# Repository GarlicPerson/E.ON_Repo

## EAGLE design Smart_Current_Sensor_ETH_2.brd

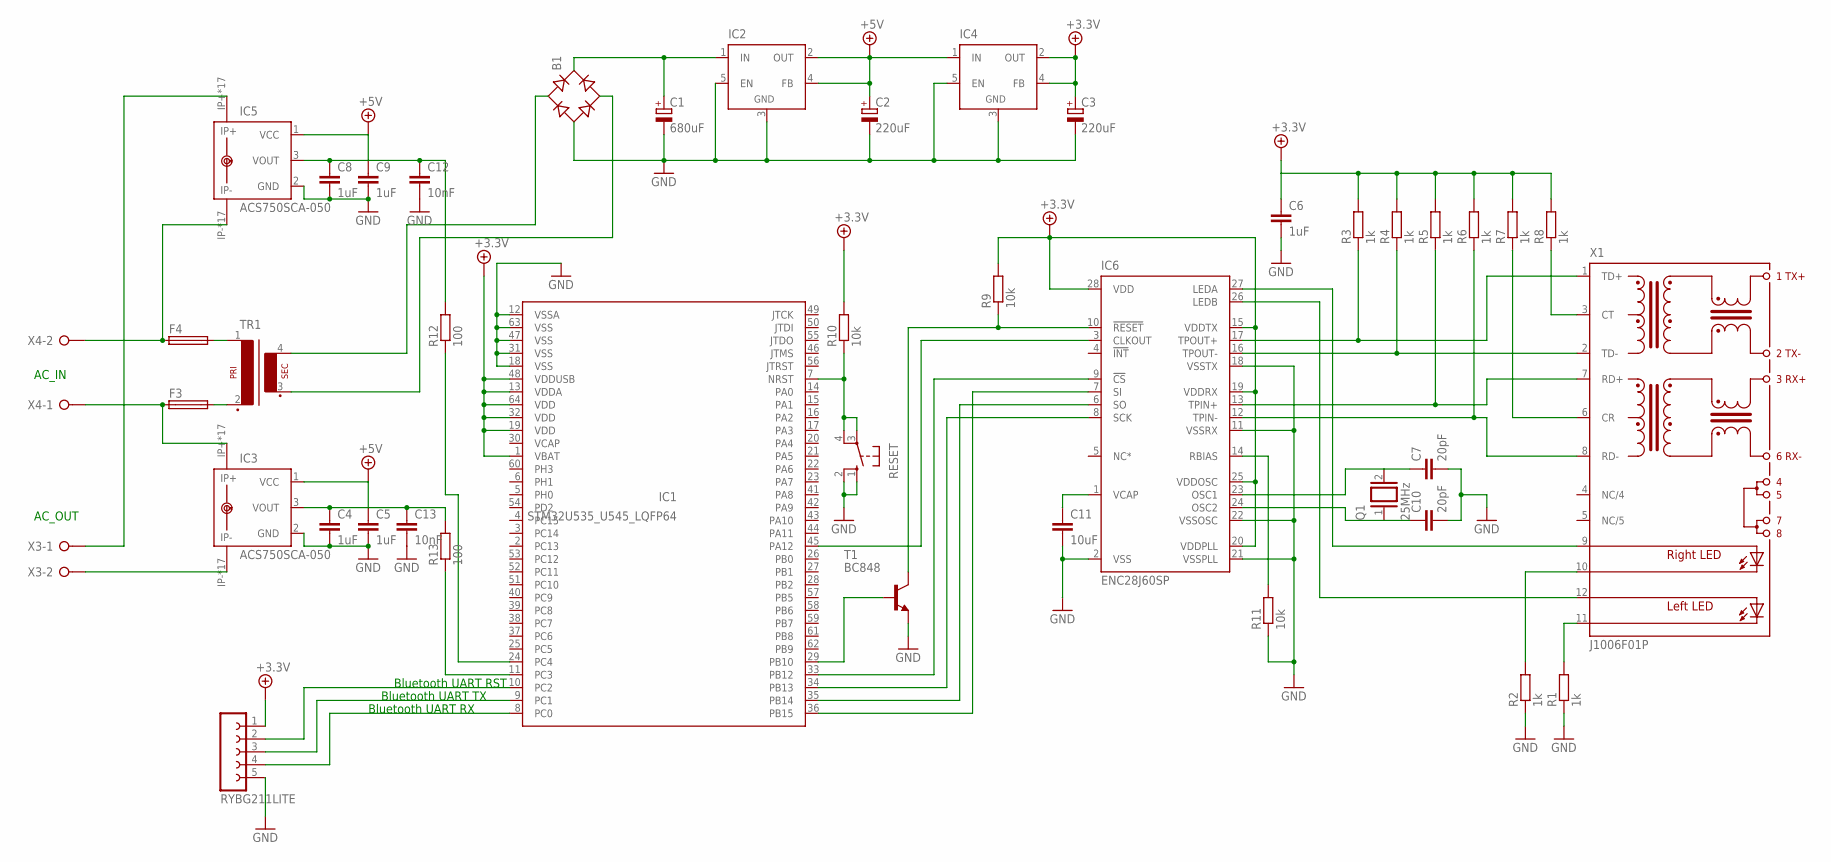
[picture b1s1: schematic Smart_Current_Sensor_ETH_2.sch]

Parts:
B1: B-DIL
C1: 680uF; 153CLV-0405
C2, C3: 220uF; 153CLV-0405
C4, C5, C6, C8, C9: 1uF; C1210
C7, C10: 20pF; C1210
C11: 10uF; C1210
C12, C13: 10nF; C1210
F3, F4: KS9V
IC1: STM32U535_U545_LQFP64; LQFP64_PACKAGE
IC2, IC4: LM2596TH; TO220-52
IC3, IC5: ACS750SCA-050; ACS75050
IC6: ENC28J60SP; DIL28-3
Q1: 25MHz; QS
R1, R2, R3, R4, R5, R6, R7, R8: 1k; R1206
R9, R10, R11: 10k; R1206
R12, R13: 100; R1206
RESET: 10-XX; B3F-10XX
RYBG211LITE: FE05-1
T1: BC848; SOT23
TR1: VR04,5-1
X1: J1006F01P; J1
X3, X4: W237-02P; W237-132

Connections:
+5V: C2.+, C3.+, C5.1, C6.1, C9.1, IC1.1 (VBAT), IC1.13 (VDDA), IC1.19 (VDD), IC1.32 (VDD), IC1.48 (VDDUSB), IC1.64 (VDD), IC2.2 (OUT), IC2.4 (FB), IC3.1 (VCC), IC4.1 (IN), IC4.2 (OUT), IC4.4 (FB), IC5.1 (VCC), IC6.15 (VDDTX), IC6.19 (VDDRX), IC6.20 (VDDPLL), IC6.25 (VDDOSC), IC6.28 (VDD), R3.2, R4.2, R5.2, R6.2, R7.2, R8.2, R9.2, R10.2, RYBG211LITE.1
GND: B1.-, C1.-, C2.-, C3.-, C4.2, C5.2, C6.2, C7.2, C8.2, C9.2, C10.2, C11.2, C12.2, C13.2, IC1.12 (VSSA), IC1.18 (VSS), IC1.31 (VSS), IC1.47 (VSS), IC1.63 (VSS), IC2.3 (GND), IC2.5 (EN), IC3.2 (GND), IC4.3 (GND), IC4.5 (EN), IC5.2 (GND), IC6.2 (VSS), R1.1, R2.1, RESET.1 (S), RESET.2 (S1), RYBG211LITE.5, T1.2 (E)
unnamed: B1.AC1, TR1.4 (S4)
unnamed: B1.AC2, TR1.3 (S3)
unnamed: R1.2, X1.11 (C-L)
unnamed: B1.+, C1.+, IC2.1 (IN)
unnamed: IC5.IP+, IC5.IP+@2 (IP+), IC5.IP+@3 (IP+), IC5.IP+@4 (IP+), IC5.IP+@5 (IP+), IC5.IP+@6 (IP+), IC5.IP+@7 (IP+), IC5.IP+@8 (IP+), IC5.IP+@9 (IP+), IC5.IP+@10 (IP+), IC5.IP+@11 (IP+), IC5.IP+@12 (IP+), IC5.IP+@13 (IP+), IC5.IP+@14 (IP+), IC5.IP+@15 (IP+), IC5.IP+@16 (IP+), IC5.IP+@17 (IP+), X3.1
unnamed: IC3.IP-, IC3.IP-@2 (IP-), IC3.IP-@3 (IP-), IC3.IP-@4 (IP-), IC3.IP-@5 (IP-), IC3.IP-@6 (IP-), IC3.IP-@7 (IP-), IC3.IP-@8 (IP-), IC3.IP-@9 (IP-), IC3.IP-@10 (IP-), IC3.IP-@11 (IP-), IC3.IP-@12 (IP-), IC3.IP-@13 (IP-), IC3.IP-@14 (IP-), IC3.IP-@15 (IP-), IC3.IP-@16 (IP-), IC3.IP-@17 (IP-), X3.2
unnamed: C4.1, C13.1, IC3.3 (VOUT), R13.2
unnamed: R2.2, X1.10 (C-R)
unnamed: IC6.17 (TPOUT+), R3.1, X1.1 (TD+)
unnamed: IC6.16 (TPOUT-), R4.1, X1.2 (TD-)
unnamed: IC6.13 (TPIN+), R5.1, X1.7 (RD+)
unnamed: IC6.12 (TPIN-), R6.1, X1.8 (RD-)
unnamed: IC1.8 (PC0), RYBG211LITE.4
unnamed: IC6.27 (LEDA), X1.9 (A-R)
unnamed: IC6.26 (LEDB), X1.12 (A-L)
unnamed: IC1.9 (PC1), RYBG211LITE.3
unnamed: IC1.10 (PC2), RYBG211LITE.2
unnamed: IC1.7 (NRST), R10.1, RESET.3, RESET.4 (P1)
unnamed: R7.1, X1.6 (CR)
unnamed: F4.2, TR1.1
unnamed: F4.1, IC5.IP-, IC5.IP-@2 (IP-), IC5.IP-@3 (IP-), IC5.IP-@4 (IP-), IC5.IP-@5 (IP-), IC5.IP-@6 (IP-), IC5.IP-@7 (IP-), IC5.IP-@8 (IP-), IC5.IP-@9 (IP-), IC5.IP-@10 (IP-), IC5.IP-@11 (IP-), IC5.IP-@12 (IP-), IC5.IP-@13 (IP-), IC5.IP-@14 (IP-), IC5.IP-@15 (IP-), IC5.IP-@16 (IP-), IC5.IP-@17 (IP-), X4.2
unnamed: C8.1, C12.1, IC5.3 (VOUT), R12.2
unnamed: R8.1, X1.3 (CT)
unnamed: IC6.11 (VSSRX), IC6.18 (VSSTX), IC6.21 (VSSPLL), IC6.22 (VSSOSC), R11.1
unnamed: IC1.36 (PB15), IC6.7 (SI)
unnamed: C7.1, IC6.23 (OSC1), Q1.2
unnamed: C10.1, IC6.24 (OSC2), Q1.1
unnamed: IC1.34 (PB13), IC6.8 (SCK)
unnamed: IC1.35 (PB14), IC6.6 (SO)
unnamed: IC1.33 (PB12), IC6.9 (!CS)
unnamed: IC1.29 (PB10), T1.1 (B)
unnamed: IC6.10 (!RESET), R9.1, T1.3 (C)
unnamed: IC6.14 (RBIAS), R11.2
unnamed: C11.1, IC6.1 (VCAP)
unnamed: IC1.45 (PA12), IC6.3 (CLKOUT)
unnamed: IC1.24 (PC4), R12.1
unnamed: IC1.11 (PC3), R13.1
unnamed: F3.2, TR1.2
unnamed: F3.1, IC3.IP+, IC3.IP+@2 (IP+), IC3.IP+@3 (IP+), IC3.IP+@4 (IP+), IC3.IP+@5 (IP+), IC3.IP+@6 (IP+), IC3.IP+@7 (IP+), IC3.IP+@8 (IP+), IC3.IP+@9 (IP+), IC3.IP+@10 (IP+), IC3.IP+@11 (IP+), IC3.IP+@12 (IP+), IC3.IP+@13 (IP+), IC3.IP+@14 (IP+), IC3.IP+@15 (IP+), IC3.IP+@16 (IP+), IC3.IP+@17 (IP+), X4.1

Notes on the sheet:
Bluetooth UART RX
Bluetooth UART TX
Bluetooth UART RST
AC_IN
AC_OUT

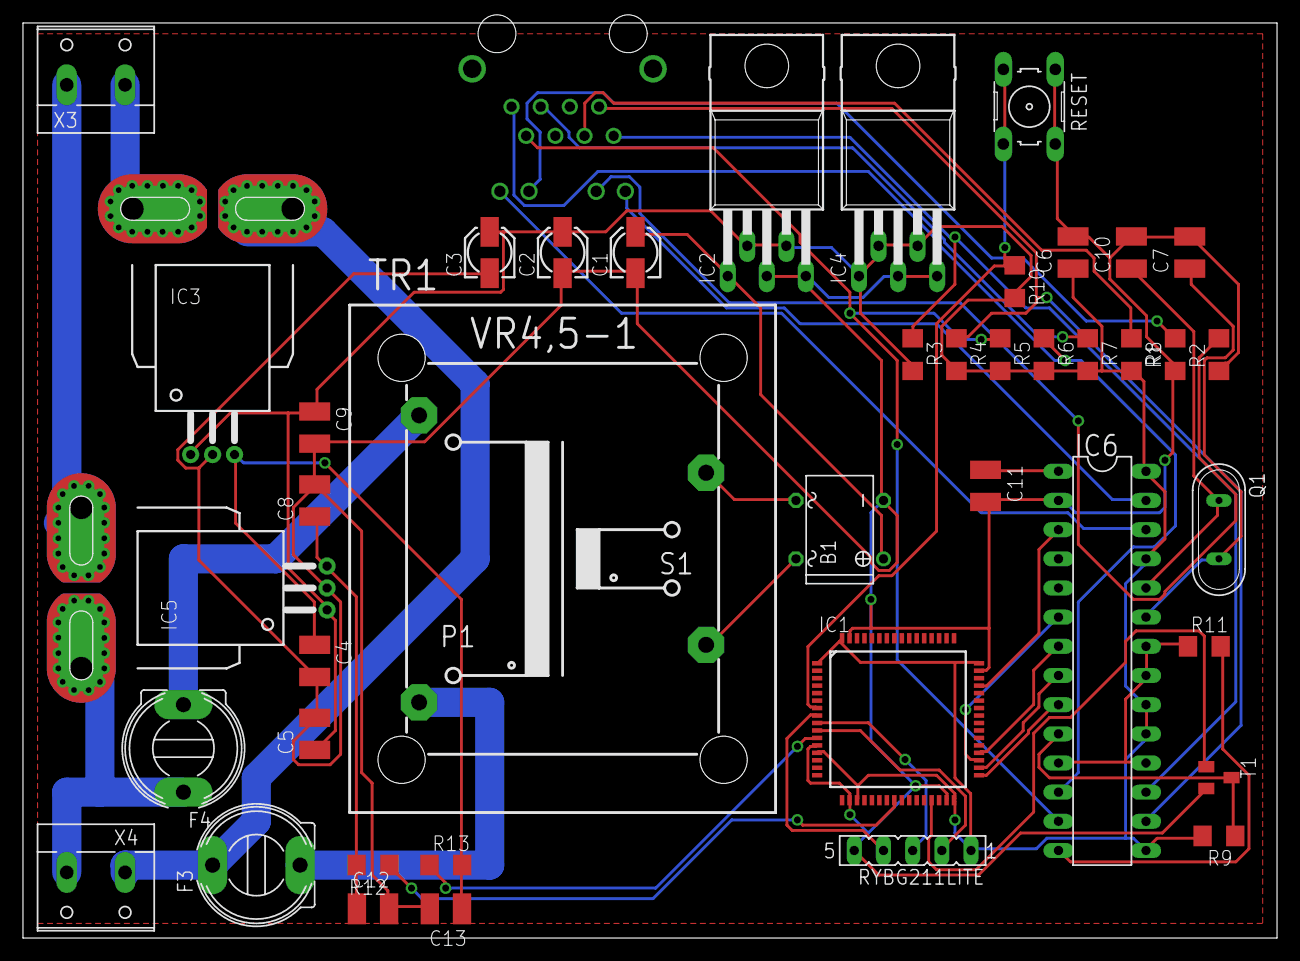
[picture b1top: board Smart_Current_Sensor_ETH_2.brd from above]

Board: 2 copper layers, 109.2 x 79.7 mm, 43 parts (1 on the bottom side), 41 nets.

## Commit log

2023-07-31 Added python notebook for HSM signing
2023-07-31 Non technical ppt finalized
2023-07-31 Added Animation to ppt
2023-07-31 Created Technical report, updated other files
2023-08-02 Removed unnecessary files
